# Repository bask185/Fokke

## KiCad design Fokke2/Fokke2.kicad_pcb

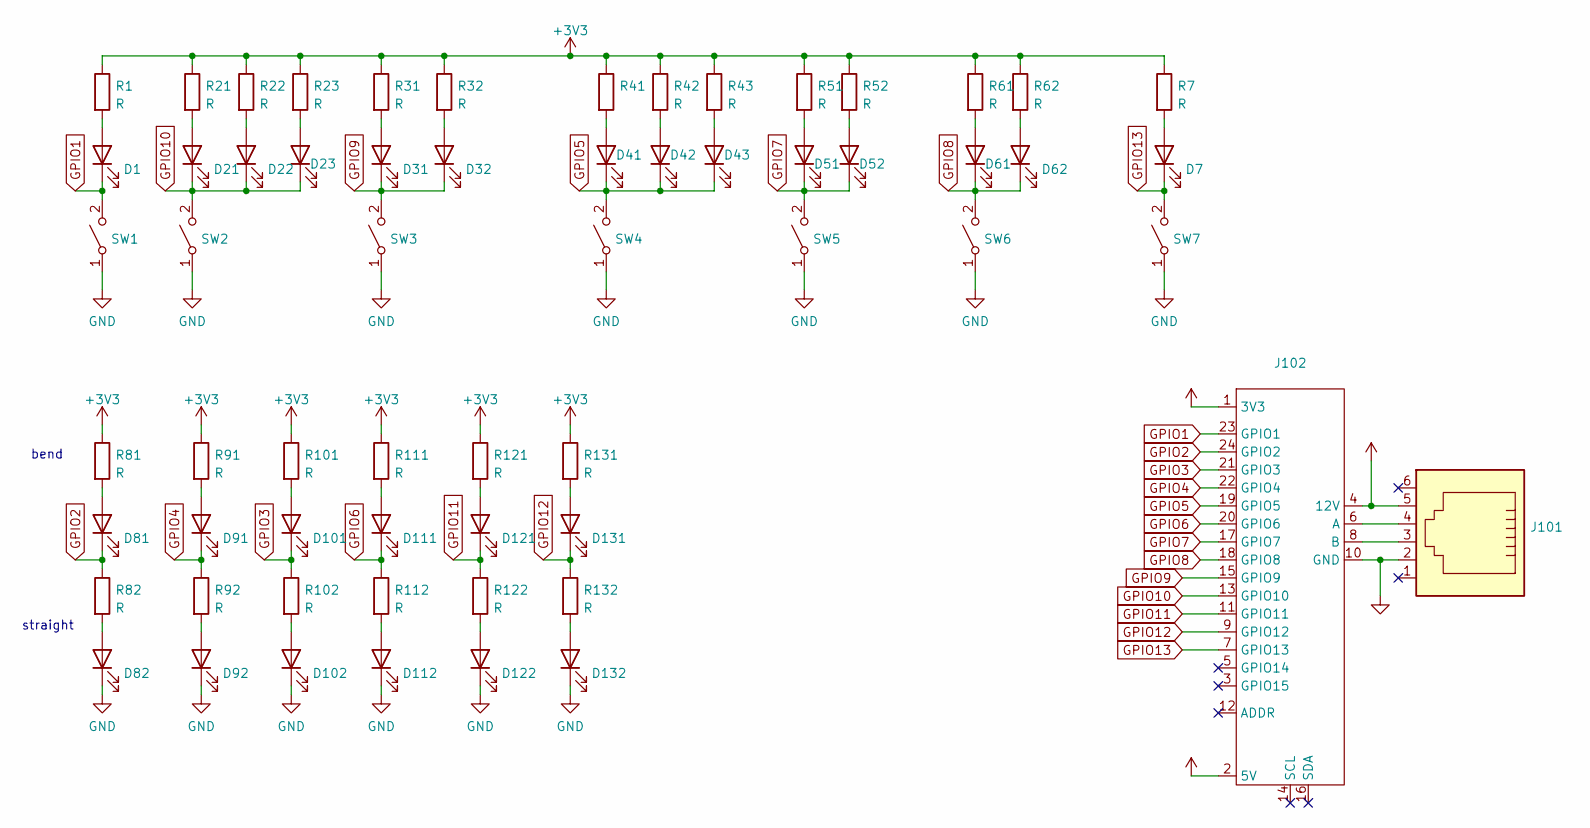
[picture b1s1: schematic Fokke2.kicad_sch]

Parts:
D1, D7, D21, D22, D23, D31, D32, D41, D42, D43, D51, D52, D61, D62, D81, D82, D91, D92, D101, D102, D111, D112, D121, D122, D131, D132: LED; LED_D3.0mm
J101, J102: (no value)
R1, R7, R21, R22, R23, R31, R32, R42, R43, R51, R52, R61, R62, R81, R82, R91, R92, R101, R102, R111, R112, R121, R122, R131, R132: R; R_0805_2012Metric_Pad1.20x1.40mm_HandSolder
R41: (no value)
SW1, SW2, SW3, SW4, SW5, SW6, SW7: SW_SPST; SW_PUSH_6mm_H4.3mm

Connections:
GPIO1: D1.1 (K), J102.23 (GPIO1), SW1.2 (B)
GPIO2: D81.1 (K), J102.24 (GPIO2), R82.1
GPIO3: D101.1 (K), J102.21 (GPIO3), R102.1
GPIO4: D91.1 (K), J102.22 (GPIO4), R92.1
GPIO5: D41.1 (K), D42.1 (K), D43.1 (K), J102.19 (GPIO5), SW4.2 (B)
GPIO6: D111.1 (K), J102.20 (GPIO6), R112.1
GPIO7: D51.1 (K), D52.1 (K), J102.17 (GPIO7), SW5.2 (B)
GPIO8: D61.1 (K), D62.1 (K), J102.18 (GPIO8), SW6.2 (B)
GPIO9: D31.1 (K), D32.1 (K), J102.15 (GPIO9), SW3.2 (B)
GPIO10: D21.1 (K), D22.1 (K), D23.1 (K), J102.13 (GPIO10), SW2.2 (B)
GPIO11: D121.1 (K), J102.11 (GPIO11), R122.1
GPIO12: D131.1 (K), J102.9 (GPIO12), R132.1
GPIO13: D7.1 (K), J102.7 (GPIO13), SW7.2 (B)
unnamed: D1.2 (A), R1.2
unnamed: D7.2 (A), R7.2
unnamed: D21.2 (A), R21.2
unnamed: D22.2 (A), R22.2
unnamed: D23.2 (A), R23.2
unnamed: D31.2 (A), R31.2
unnamed: D32.2 (A), R32.2
unnamed: D41.2 (A), R41.2
unnamed: D42.2 (A), R42.2
unnamed: D43.2 (A), R43.2
unnamed: D51.2 (A), R51.2
unnamed: D52.2 (A), R52.2
unnamed: D61.2 (A), R61.2
unnamed: D62.2 (A), R62.2
unnamed: D81.2 (A), R81.2
unnamed: D82.2 (A), R82.2
unnamed: D91.2 (A), R91.2
unnamed: D92.2 (A), R92.2
unnamed: D101.2 (A), R101.2
unnamed: D102.2 (A), R102.2
unnamed: D111.2 (A), R111.2
unnamed: D112.2 (A), R112.2
unnamed: D121.2 (A), R121.2
unnamed: D122.2 (A), R122.2
unnamed: D131.2 (A), R131.2
unnamed: D132.2 (A), R132.2
unnamed: J101.3, J102.8 (B)
unnamed: J101.4, J102.6 (A)

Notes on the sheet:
bend
straight

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
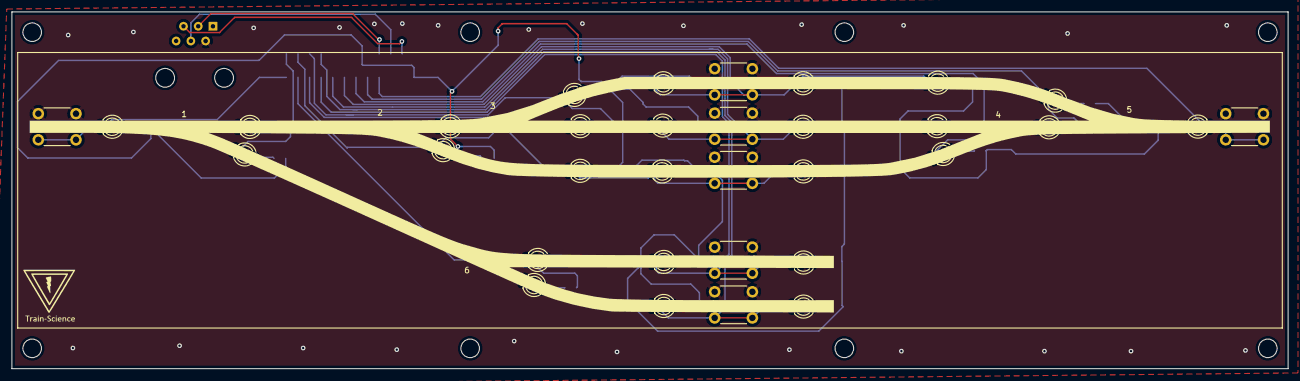
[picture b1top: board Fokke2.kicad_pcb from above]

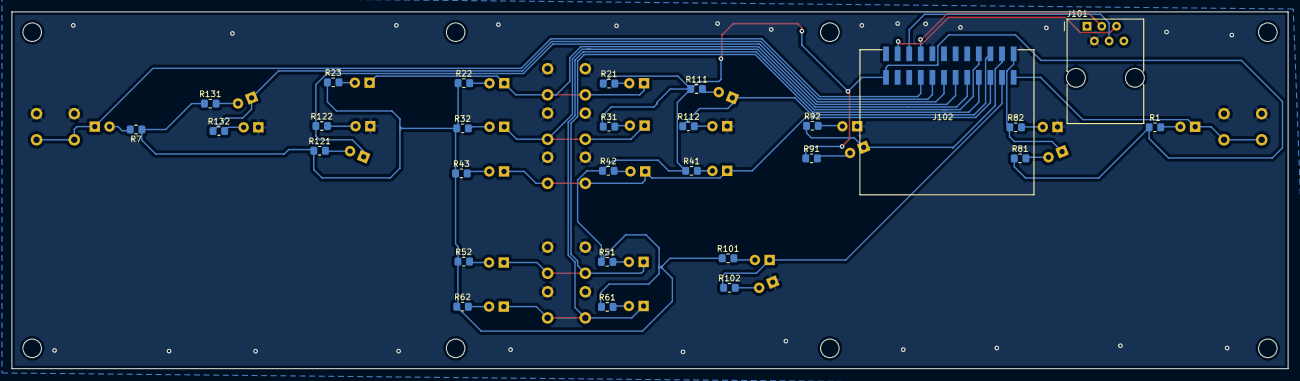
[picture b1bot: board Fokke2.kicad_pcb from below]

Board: 2 copper layers, 220.0 x 61.5 mm, 61 parts (28 on the bottom side), 44 nets.

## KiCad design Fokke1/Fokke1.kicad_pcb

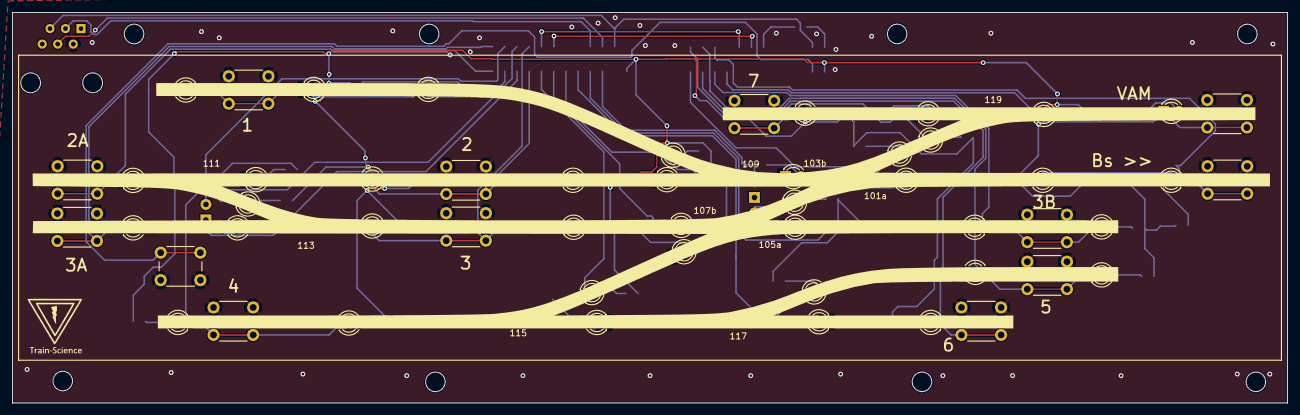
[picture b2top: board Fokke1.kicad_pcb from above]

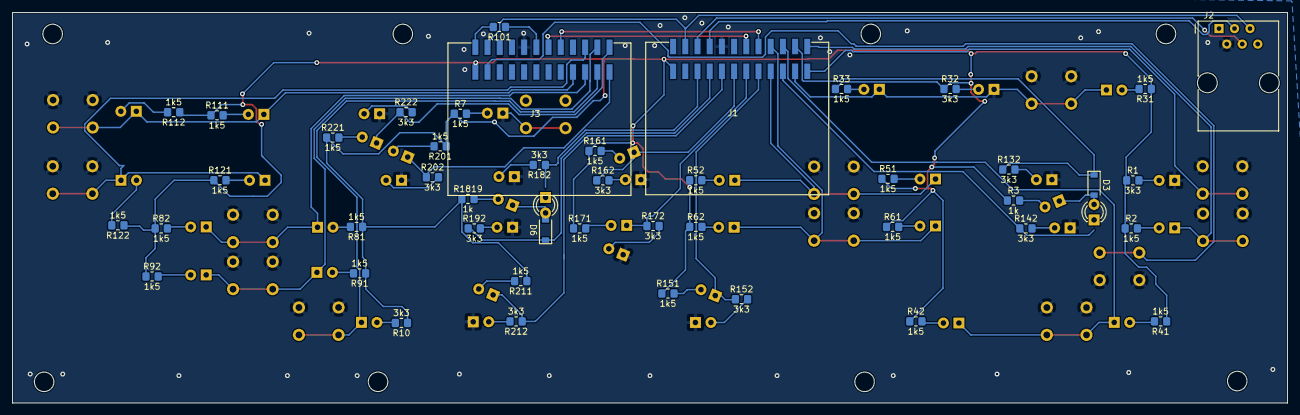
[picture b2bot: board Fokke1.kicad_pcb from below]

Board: 2 copper layers, 209.0 x 64.0 mm, 99 parts (47 on the bottom side), 64 nets.

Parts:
D1, D2, D4, D5, D7, D10, D31, D32, D33, D41, D42, D51, D52, D61, D62, D81, D82, D91, D92, D111, D112, D121, D122, D132, D142, D151, D152, D161, D162, D171, D172, D182, D192, D201, D202, D211, D212, D221, D222, D1314, D1819: LED; LED_NO_SILK
D3, D6: D; D_SOD-123
J1, J3: panelX_controller; panelX_contoller
J2: 6P6C; RJ12_Amphenol_54601
R1, R10, R32, R132, R142, R152, R162, R172, R182, R192, R202, R212, R222: 3k3; R_0805_SILK_VALUE
R2, R7, R31, R33, R41, R42, R51, R52, R61, R62, R81, R82, R91, R92, R111, R112, R121, R122, R151, R161, R171, R201, R211, R221: 1k5; R_0805_SILK_VALUE
R3, R1819: 1k; R_0805_SILK_VALUE
R101: 100R; R_0805_2012Metric_Pad1.20x1.40mm_HandSolder
SW1, SW2, SW3, SW4, SW5, SW6, SW7, SW8, SW9, SW10, SW11, SW12, SW30: SW_SPST; SW_NO_SILK

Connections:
+3V3: J1.1 (3V3), J3.1 (3V3), R2.1, R3.1, R7.1, R31.1, R33.1, R41.1, R42.1, R51.1, R52.1, R61.1, R62.1, R81.1, R82.1, R91.1, R92.1, R111.1, R112.1, R121.1, R122.1, R151.1, R161.1, R171.1, R201.1, R211.1, R221.1, R1819.1
+12V: J1.4 (12V), J2.5, J3.4 (12V)
GND: D1.1 (K), D7.1 (K), D32.1 (K), D132.1 (K), D142.1 (K), D152.1 (K), D162.1 (K), D172.1 (K), D182.1 (K), D192.1 (K), D202.1 (K), D212.1 (K), D222.1 (K), J1.10 (GND), J2.2, J3.10 (GND), SW1.1 (A), SW2.1 (A), SW3.1 (A), SW4.1 (A), SW5.1 (A), SW6.1 (A), SW7.1 (A), SW8.1 (A), SW9.1 (A), SW10.1 (A), SW11.1 (A), SW12.1 (A), SW30.1 (A)
GPIO1: D2.1 (K), J1.23 (GPIO1), SW1.2 (B)
GPIO2: D5.1 (K), J1.24 (GPIO2), SW2.2 (B)
GPIO3: D10.1 (K), J1.21 (GPIO3), SW3.2 (B)
GPIO4: D3.1 (K), J1.22 (GPIO4), R1.1, R132.1
GPIO5: D6.1 (K), J1.19 (GPIO5), R142.1
GPIO6: J1.20 (GPIO6), SW4.2 (B)
GPIO7: D51.1 (K), D52.1 (K), J1.17 (GPIO7), SW5.2 (B)
GPIO8: D61.1 (K), D62.1 (K), J1.18 (GPIO8), SW6.2 (B)
GPIO9: D151.1 (K), J1.15 (GPIO9), R10.1, R152.1
GPIO10: D171.1 (K), J1.13 (GPIO10), R172.1
GPIO11: D161.1 (K), J1.11 (GPIO11), R162.1
GPIO12: D211.1 (K), J1.9 (GPIO12), R32.1, R212.1
GPIO13: J1.7 (GPIO13), R192.1
GPIO14: J1.5 (GPIO14), R182.1
GPIO16: D31.1 (K), D201.1 (K), J3.23 (GPIO1), R202.1
GPIO17: D221.1 (K), J3.24 (GPIO2), R222.1
GPIO18: J3.21 (GPIO3), SW10.2 (B)
GPIO19: D33.1 (K), D91.1 (K), D92.1 (K), J3.22 (GPIO4), SW9.2 (B)
GPIO20: D81.1 (K), D82.1 (K), J3.19 (GPIO5), SW8.2 (B)
GPIO21: D42.1 (K), D121.1 (K), D122.1 (K), J3.20 (GPIO6), SW12.2 (B)
GPIO22: D41.1 (K), D111.1 (K), D112.1 (K), J3.17 (GPIO7), SW11.2 (B)
GPIO30: J3.3 (GPIO15), SW30.2 (B)
unnamed: D1.2 (A), R1.2
unnamed: D2.2 (A), R2.2
unnamed: D3.2 (A), D4.1 (K), D6.2 (A)
unnamed: D4.2 (A), R3.2
unnamed: D41.2 (A), R41.2
unnamed: D42.2 (A), R42.2
unnamed: D51.2 (A), R51.2
unnamed: D52.2 (A), R52.2
unnamed: D61.2 (A), R61.2
unnamed: D62.2 (A), R62.2
unnamed: D81.2 (A), R81.2
unnamed: D82.2 (A), R82.2
unnamed: D91.2 (A), R91.2
unnamed: D92.2 (A), R92.2
unnamed: D111.2 (A), R111.2
unnamed: D112.2 (A), R112.2
unnamed: D121.2 (A), R121.2
unnamed: D122.2 (A), R122.2
unnamed: D132.2 (A), R132.2
unnamed: D142.2 (A), R142.2
unnamed: D151.2 (A), R151.2
unnamed: D152.2 (A), R152.2
unnamed: D161.2 (A), R161.2
unnamed: D162.2 (A), R162.2
unnamed: D171.2 (A), R171.2
unnamed: D172.2 (A), R172.2
unnamed: D182.2 (A), R182.2
unnamed: D192.2 (A), R192.2
unnamed: D201.2 (A), R201.2
unnamed: D202.2 (A), R202.2
unnamed: D211.2 (A), R211.2
unnamed: D212.2 (A), R212.2
unnamed: D221.2 (A), R221.2
unnamed: D222.2 (A), R222.2
unnamed: D1819.2 (A), R1819.2
unnamed: J1.6 (A), J2.4
unnamed: J1.8 (B), J2.3
SCL: J1.14 (SCL), J3.14 (SCL)
SDA: J1.16 (SDA), J3.16 (SDA)

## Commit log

2023-02-01 added logo and layout plans
2023-02-01 I am halfway of schematic of Fokke1. I need to make me new footprints for leds and resistors and switches because I want to remove and add certain silk texts
2023-02-01 Did all component numbering for Fokke1. The connector is still to be finished
2023-02-01 routed all but the main connector of Fokke1
2023-02-01 did alot of work on Fokke2. The connector is still needed. Also going to make a module flatcable controller line
2023-02-02 commit 4 push
2023-02-05 I added a button to Fokke 1 for his gate, but I lost annonation with the schematic. The schematic as is now is FUBAR. The project however is finished so I got lucky...
